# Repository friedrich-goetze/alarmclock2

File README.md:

# alarmclock2
PCB for my brutal alarmclock

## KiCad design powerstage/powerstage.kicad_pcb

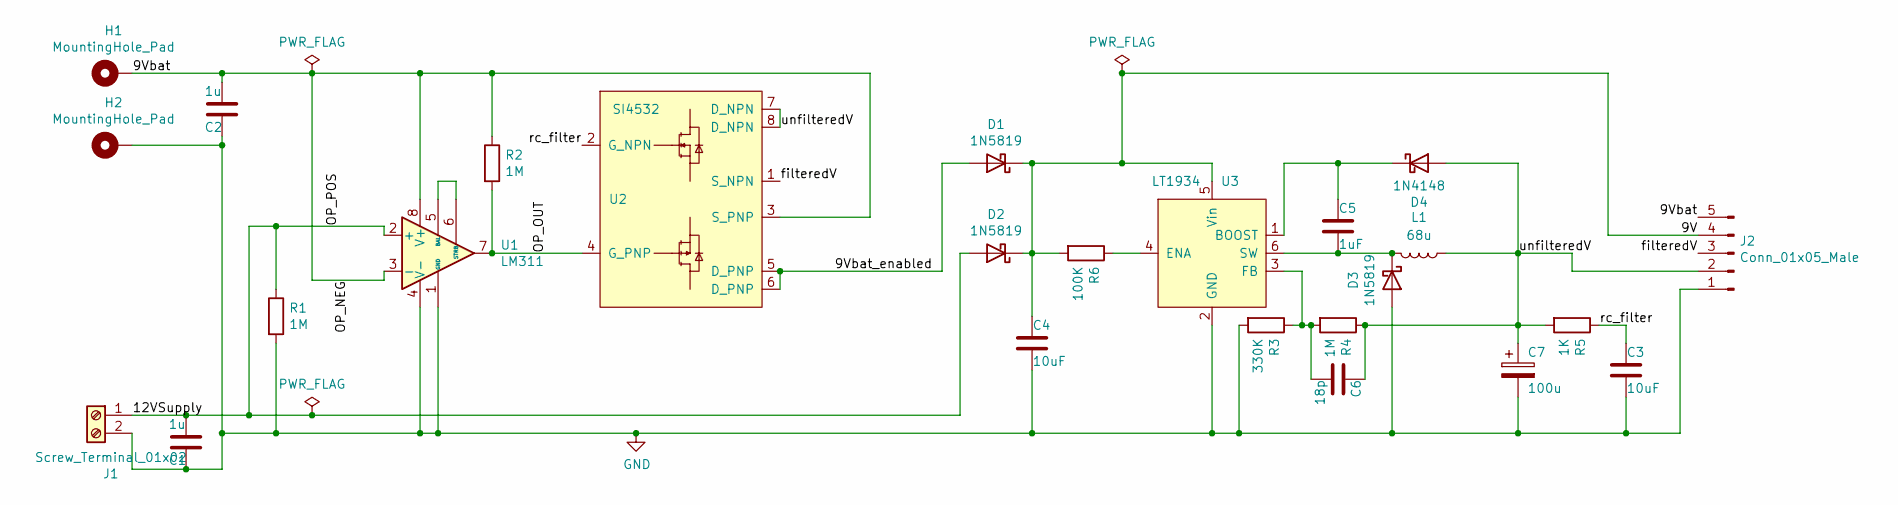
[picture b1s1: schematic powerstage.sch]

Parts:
C1, C2: 1u; Handsolder_0805_2012Metric
C3, C4: 10uF; C_1812_4532Metric_Pad1.30x3.40mm_HandSolder
C5: 1uF; Handsolder_0805_2012Metric
C6: 18p; Handsolder_0805_2012Metric
C7: 100u; CP_Radial_D6.3mm_P2.50mm
D1, D2, D3: 1N5819; D_SOD-123
D4: 1N4148; D_DO-35_SOD27_P7.62mm_Horizontal
H1, H2: MountingHole_Pad; Pin_D1.0mm_L10.0mm
J1: Screw_Terminal_01x02; PinHeader_1x02_P2.54mm_Vertical
J2: Conn_01x05_Male; PinHeader_1x05_P2.54mm_Vertical
L1: 68u; big-inductor
R1, R2, R4: 1M; Handsolder_1206_3216Metric
R3: 330K; Handsolder_1206_3216Metric
R5: 1K; Handsolder_1206_3216Metric
R6: 100K; Handsolder_1206_3216Metric
U1: LM311; SOIC-8_3.9x4.9mm_P1.27mm_handsolder
U2: SI4532; SOIC-8_3.9x4.9mm_P1.27mm_handsolder
U3: LT1934; TSOT-23-6_HandSoldering

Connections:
/9V: C4.1, D1.1 (K), D2.1 (K), J2.4, R6.2, U3.5 (Vin)
/9Vbat: C2.2, H1.1, J2.5, R2.1, U1.3 (-), U1.8 (V+), U2.3 (S_PNP)
/9Vbat_enabled: D1.2 (A), U2.5 (D_PNP), U2.6 (D_PNP)
/12VSupply: C1.2, D2.2 (A), J1.1, R1.1, U1.2 (+)
/OP_OUT: R2.2, U1.7, U2.4 (G_PNP)
/filteredV: J2.3, U2.1 (S_NPN)
/rc_filter: C3.1, R5.1, U2.2 (G_NPN)
/unfilteredV: C6.1, C7.1, D4.2 (A), J2.2, L1.1, R4.1, R5.2, U2.7 (D_NPN), U2.8 (D_NPN)
GND: C1.1, C2.1, C3.2, C4.2, C7.2, D3.2 (A), H2.1, J1.2, J2.1, R1.2, R3.2, U1.1 (GND), U1.4 (V-), U3.2 (GND); also elsewhere on the board
unnamed: C5.1, D4.1 (K), U3.1 (BOOST)
unnamed: C5.2, D3.1 (K), L1.2, U3.6 (SW)
unnamed: C6.2, R3.1, R4.2, U3.3 (FB)
unnamed: R6.1, U3.4 (ENA)
unnamed: U1.5 (BAL), U1.6 (STRB)

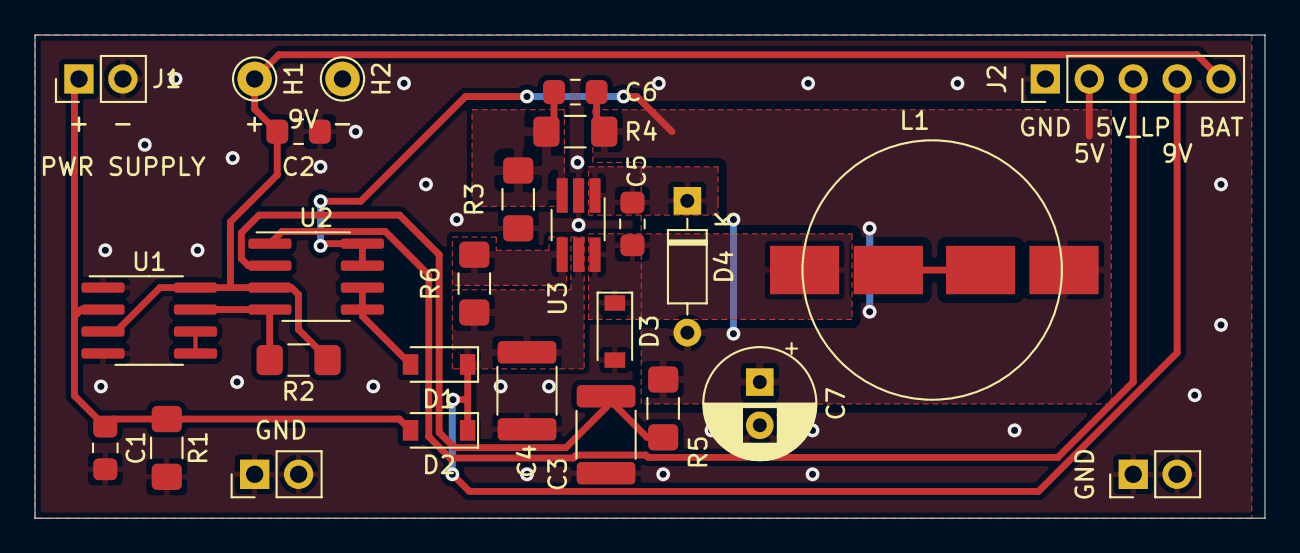
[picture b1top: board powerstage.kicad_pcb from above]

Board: 2 copper layers, 71.1 x 27.9 mm, 27 parts (0 on the bottom side), 14 nets.

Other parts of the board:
GND: Screw_Terminal_01x02; PinHeader_1x02_P2.54mm_Vertical
GND#2: Screw_Terminal_01x02; PinHeader_1x02_P2.54mm_Vertical

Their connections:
GND: GND.1, GND.2, GND#2.1, GND#2.2; also elsewhere on the board

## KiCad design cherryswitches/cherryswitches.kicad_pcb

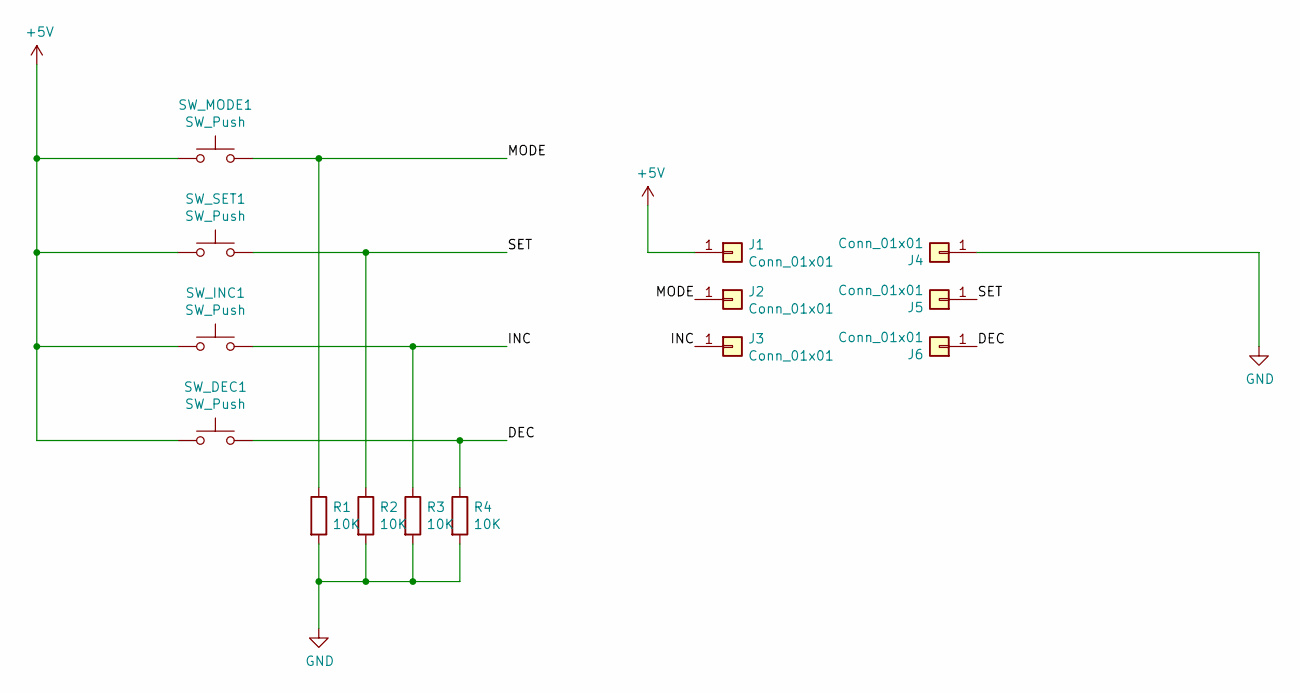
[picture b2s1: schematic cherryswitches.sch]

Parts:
J1, J2, J3, J4, J5, J6: Conn_01x01; SolderWirePad_1x01_SMD_5x10mm
R1, R2, R3, R4: 10K; R_1206_3216Metric_Pad1.30x1.75mm_HandSolder
SW_DEC1: SW_Push; SW_Cherry_MX_1.00u_Plate
SW_INC1: SW_Push; SW_Cherry_MX_1.00u_Plate
SW_MODE1: SW_Push; SW_Cherry_MX_1.00u_Plate
SW_SET1: SW_Push; SW_Cherry_MX_1.00u_Plate

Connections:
+5V: J1.1, SW_DEC1.1, SW_INC1.1, SW_MODE1.1, SW_SET1.1
/DEC: J6.1, R4.1, SW_DEC1.2
/INC: J3.1, R3.1, SW_INC1.2
/MODE: J2.1, R1.1, SW_MODE1.2
/SET: J5.1, R2.1, SW_SET1.2
GND: J4.1, R1.2, R2.2, R3.2, R4.2

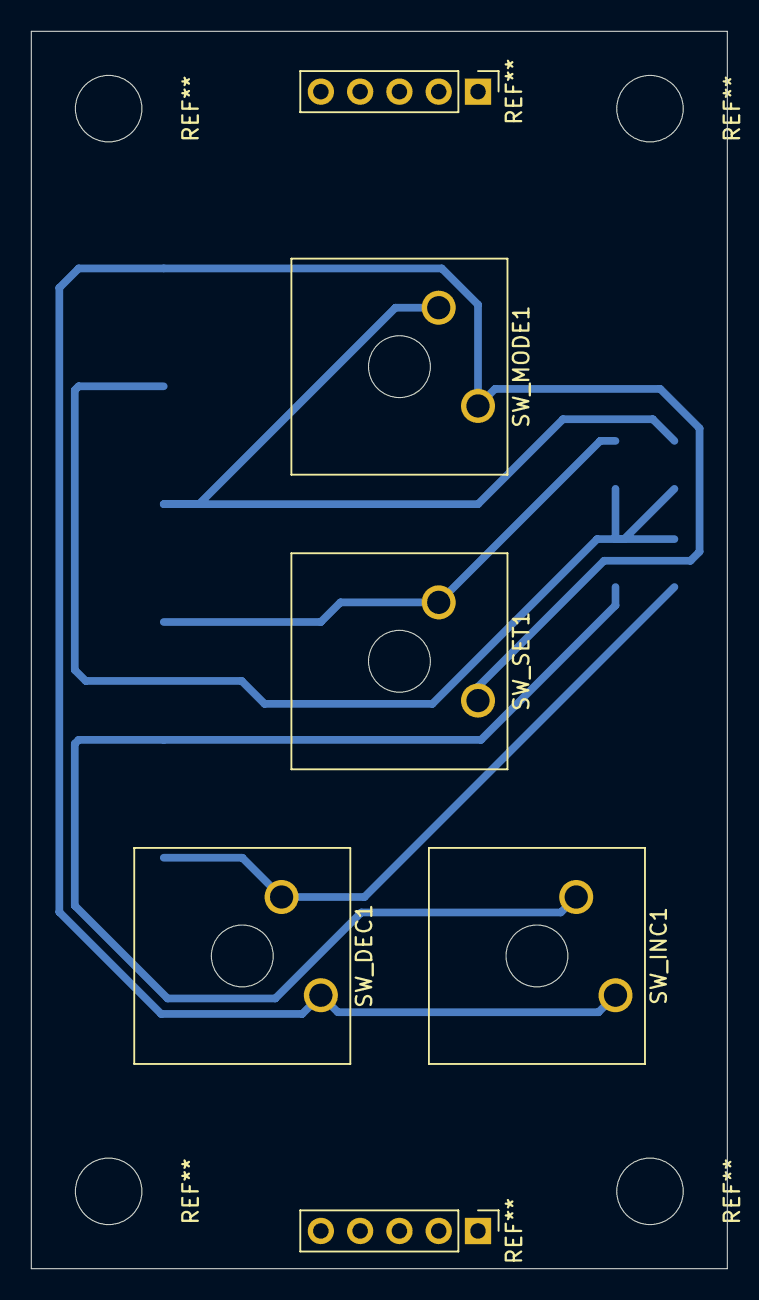
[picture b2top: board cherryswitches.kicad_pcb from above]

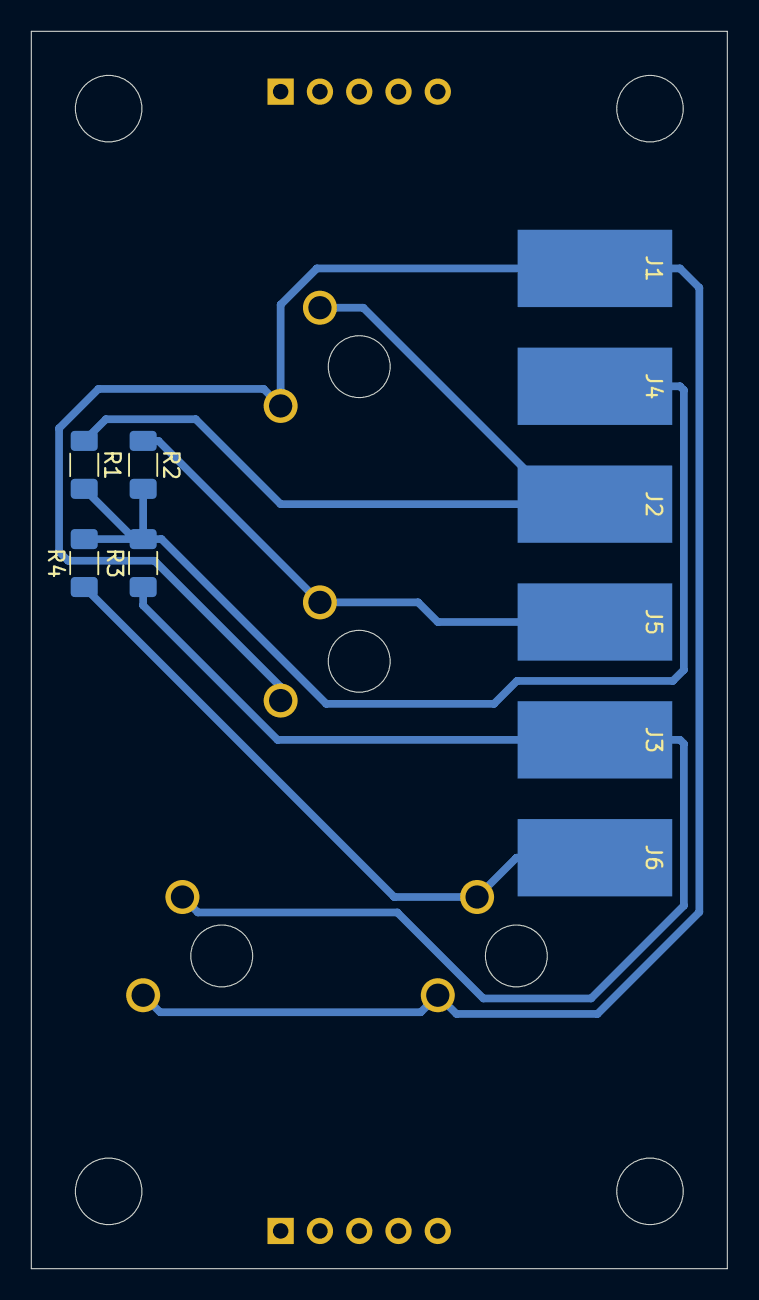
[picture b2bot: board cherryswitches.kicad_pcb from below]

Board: 2 copper layers, 45.0 x 80.0 mm, 14 parts (10 on the bottom side), 6 nets.

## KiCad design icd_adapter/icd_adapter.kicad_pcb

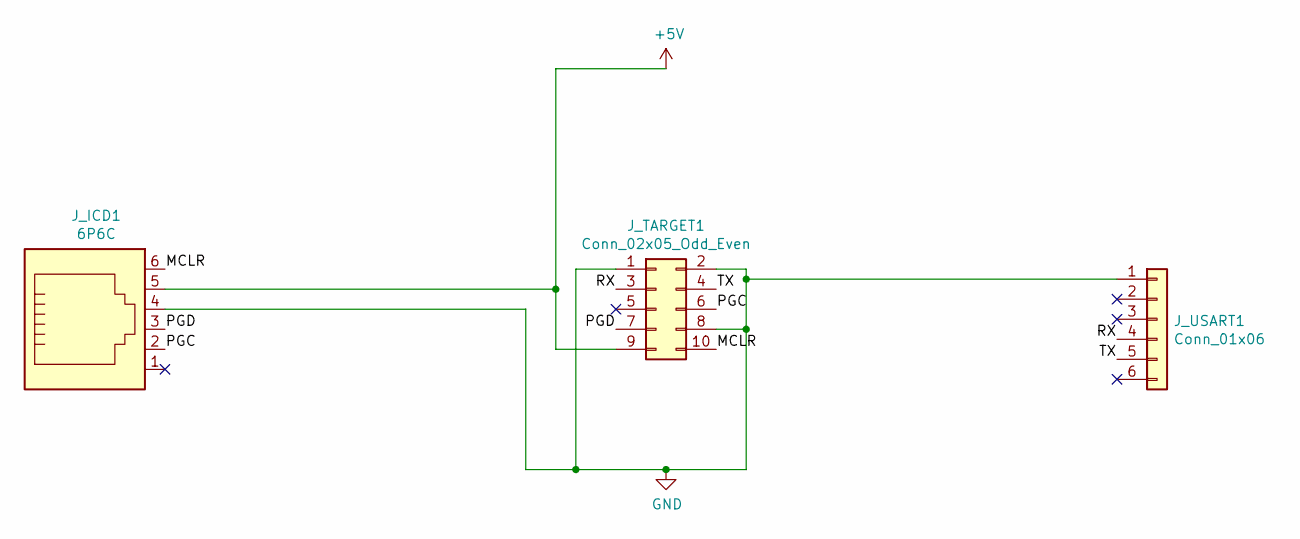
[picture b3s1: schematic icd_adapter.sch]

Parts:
J_ICD1: 6P6C; 6p6c
J_TARGET1: Conn_02x05_Odd_Even; IDC-Header_2x05_P2.54mm_Vertical
J_USART1: Conn_01x06; PinHeader_1x06_P2.54mm_Vertical

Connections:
+5V: J_ICD1.5, J_TARGET1.9
/MCLR: J_ICD1.6, J_TARGET1.10
/PGC: J_ICD1.2, J_TARGET1.6
/PGD: J_ICD1.3, J_TARGET1.7
/RX: J_TARGET1.3, J_USART1.4
/TX: J_TARGET1.4, J_USART1.5
GND: J_ICD1.4, J_TARGET1.1, J_TARGET1.2, J_TARGET1.8, J_USART1.1

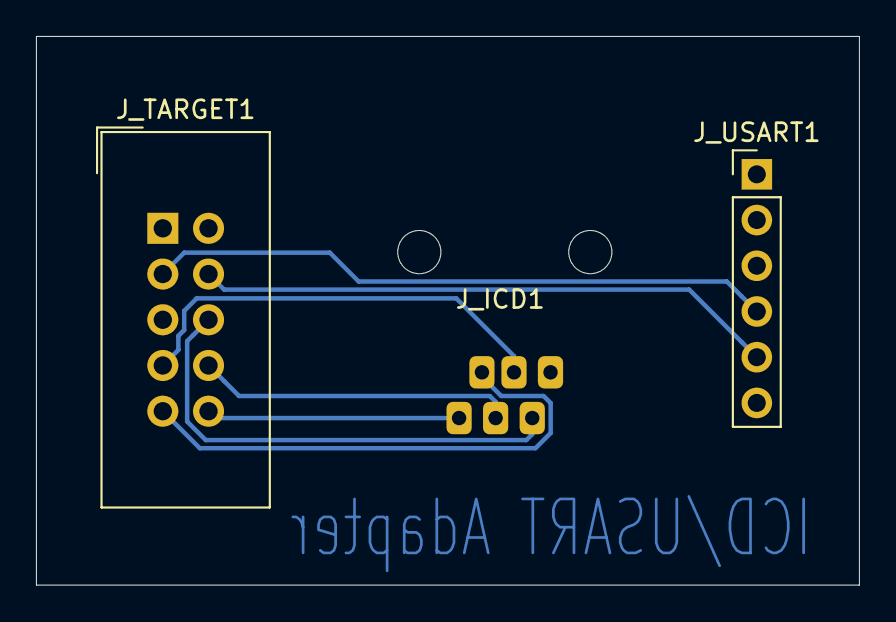
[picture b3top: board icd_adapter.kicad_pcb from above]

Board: 2 copper layers, 45.7 x 30.5 mm, 3 parts (0 on the bottom side), 7 nets.

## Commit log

2020-10-16 Mal zwischenspeichern
2020-10-17 lcd is working, yay
2020-10-17 working
2020-10-17 even scheduler doesnt stutter
2020-10-17 persistance working
2020-10-18 yay all ist working
2020-10-19 rev 2
2020-10-21 performance improvements
